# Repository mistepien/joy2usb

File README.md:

# joy2usb
Atari-like joystick adapter to USB.

<a href="https://github.com/mistepien/joy2usb/blob/main/joy2usb.pdf">Adapter</a> is actually a shield for 
<a href="https://learn.sparkfun.com/tutorials/pro-micro--fio-v3-hookup-guide/hardware-overview-pro-micro">Arduino Pro Micro based on ATmega 32U4</a>.

ATmega 32U4 has a hardware support for fullspeed USB, thus <a href="https://wiki.archlinux.org/title/mouse_polling_rate">polling rate 1000Hz</a> is not an issue for that chip.

You can use the <a href="https://github.com/mistepien/joy2usb/blob/main/production/joy2usb_6.2_2023-10-14_00-56-38/joy2usb_6.2.zip">gerber file<a> to order the PCB.

Attached   <a href="https://github.com/mistepien/joy2usb/blob/main/joy2usb.ino">code</a> uses port registers so that is quite efficient, debouncing is done without delay() function.

The adapter has a toggle C64/Amiga for choosing C64 or Amiga approach for FIRE2/FIRE3. According to <a href="http://wiki.icomp.de/wiki/DE-9_Joystick"> wiki.icomp.de website about DE-9 joystick</a>, FIRE2/FIRE3 are pulled to VCC in case of C64 and to GND in case of Amiga. That is not an issue for joy2usb due to XOR magic.

Two footprints are not trivial: DB9 male socket (<b>J1</b>) and SPDT switch (<b>SW2</b>).

Officialy the <b>J1</b> footprint (joy2usb has been designed in <a href="https://www.kicad.org/">KiCad</a>) is "DSUB-9_Male_Horizontal_P2.77x2.84mm_EdgePinOffset9.90mm_Housed_MountingHolesOffset11.32mm"
however it was chosen to fit <a href="https://www.tme.eu/pl/en/details/ld09p13a4gx00lf/d-sub-plugs-and-sockets/amphenol-communications-solutions/">   LD09P13A4GX00LF Amphenol</a>.

<b>SW2</b> supposed to be <a href="https://www.tme.eu/pl/en/details/mfp1220/slide-switches/knitter-switch/mfp-1220">Switch SPDT MFP 1220 KNITTER-SWITCH</a>, but it can be replaced with Pinheader 1x3/1x2 (pitch terminal 2.54mm) + jumper or any other SPDT switch with 3 pins and pitch terminal 2.54mm (e.g. <a href="https://www.tme.eu/pl/details/eg1218/przelaczniki-suwakowe/e-switch/">EG1218 E-SWITCH</a>).

<b>J2</b> is redundant -- you can use it to add some new features like autofire switch or sth. In attached firmware connecting PF4 to GND disables debouncing procedure. <b>If you connect PF5 to GND you can read FIRE1 CPS ("$cat /dev/ttyACM0" in Linux).</b>

Sometimes during uploading code to Arduino board you may face some issues -- then you will need to use RESET -- so <b>SW1</b> can be useful if you like to develope your own code.

BOM:
| Qty	| Reference(s) | Description |
|-----|--------------|-------------|
|3 | D1, D2, D3 | LEDs 3mm |  
|1 |	J1|	DB9 Male Connector <a href="https://www.tme.eu/pl/en/details/ld09p13a4gx00lf/d-sub-plugs-and-sockets/amphenol-communications-solutions/">   LD09P13A4GX00LF Amphenol</a> |
|1 |	J2|	2x4 Pinheader. pitch terminal: 2.54mm |
|3 | R1, R2, R3 | resistors for D1, D2 and D3 |
|2 | R4, R5	| resistors 10KΩ |
|1 | SW1 | Tact switch from Arduino breadboard projects |
|1 | SW2 | <a href="https://www.tme.eu/pl/en/details/mfp1220/slide-switches/knitter-switch/mfp-1220">Switch SPDT MFP 1220 KNITTER-SWITCH</a> |
|1 | U1 |	DIP20 socket (width 15.24mm) + <a href="https://learn.sparkfun.com/tutorials/pro-micro--fio-v3-hookup-guide/hardware-overview-pro-micro">Arduino Pro Micro</a> |

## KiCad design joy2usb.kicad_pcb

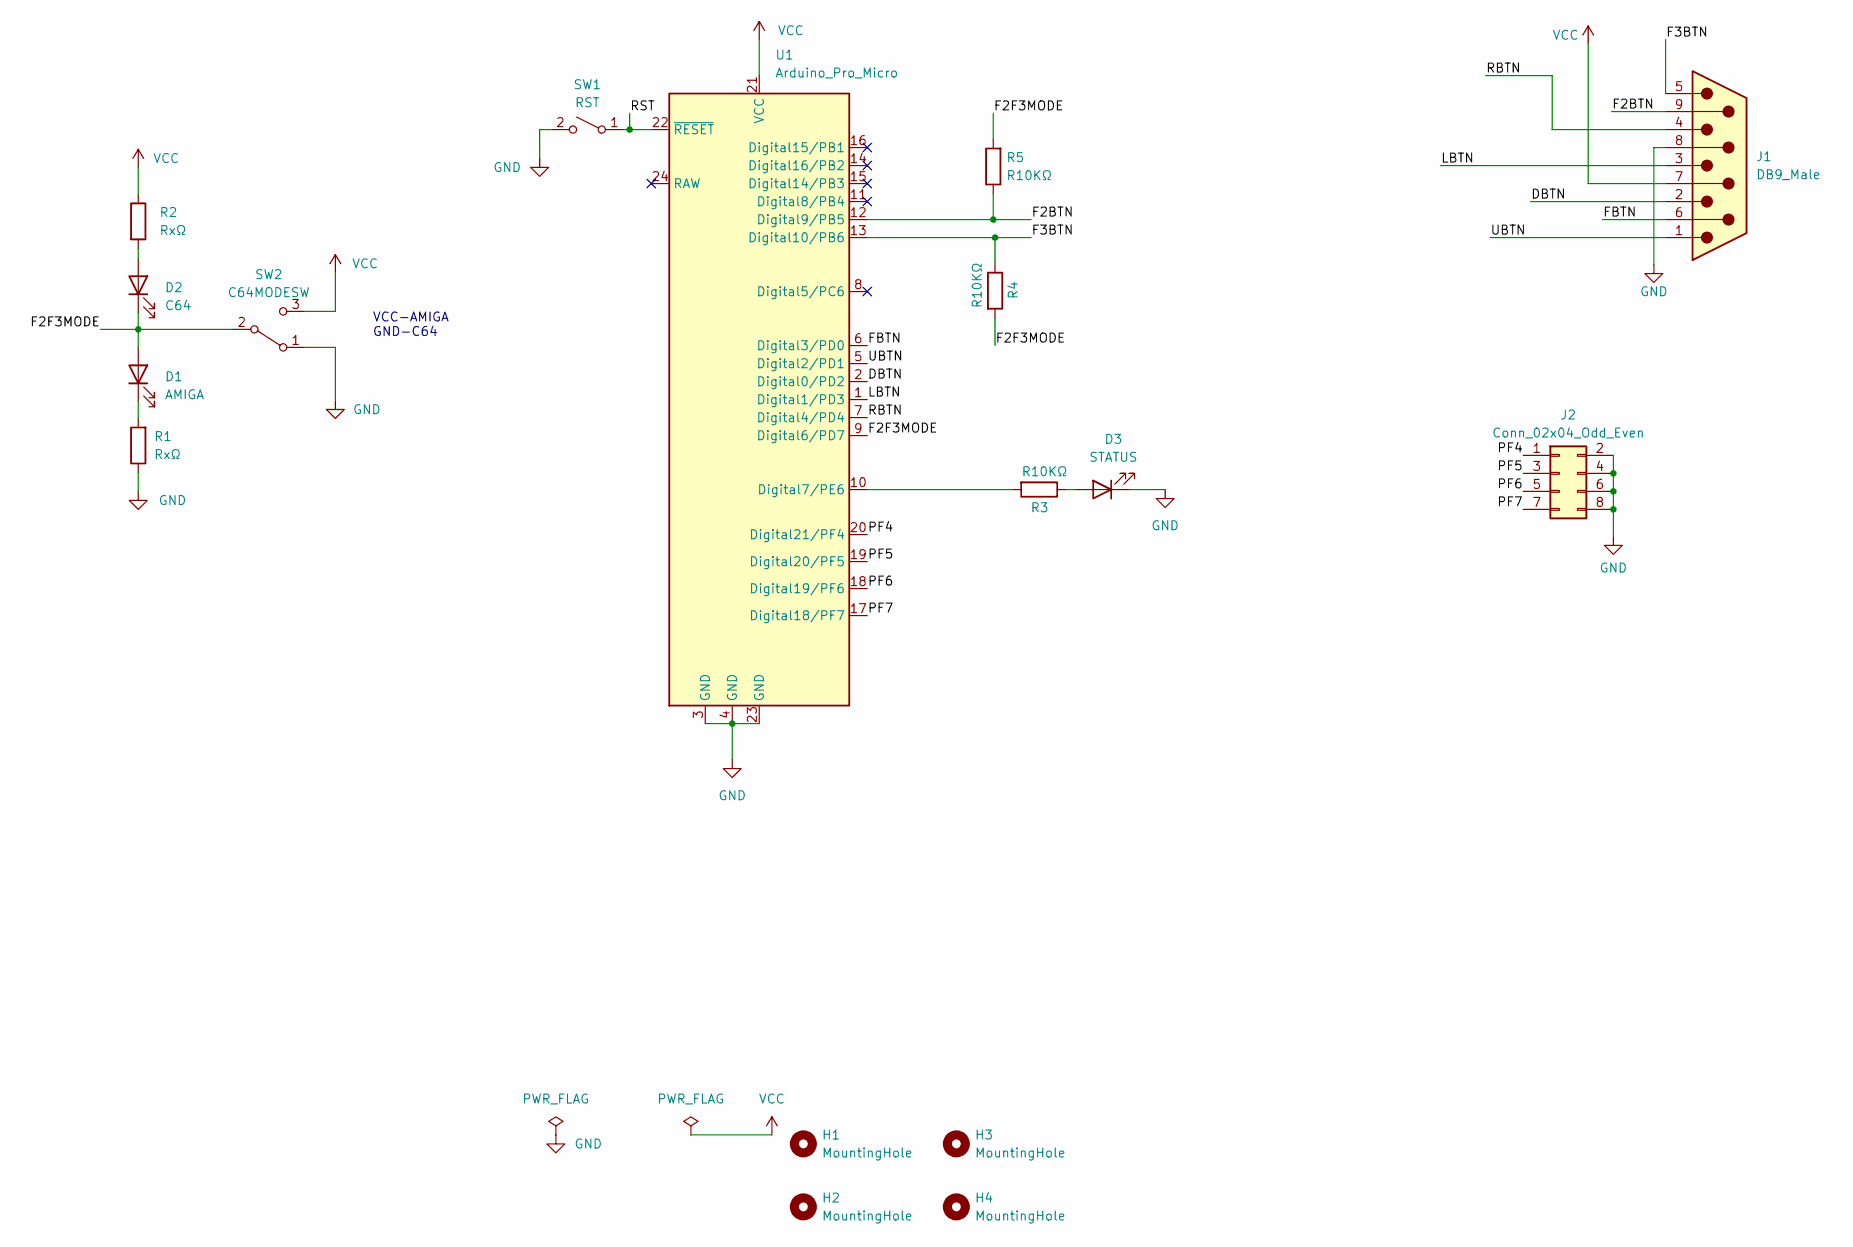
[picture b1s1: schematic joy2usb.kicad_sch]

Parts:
D1: AMIGA; LED_D3.0mm_Oval
D2: C64; LED_D3.0mm_Oval
D3: STATUS; LED_D3.0mm_Oval
H1, H2, H3, H4: MountingHole; MountingHole_3.5mm
J1: DB9_Male; DSUB-9_Male_Horizontal_P2.77x2.84mm_EdgePinOffset9.90mm_Hou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
J2: Conn_02x04_Odd_Even; PinHeader_2x04_P2.54mm_Vertical
R1, R2: RxΩ; R_Axial_DIN0207_L6.3mm_D2.5mm_P10.16mm_Horizontal_Oval
R3, R4, R5: R10KΩ; R_Axial_DIN0207_L6.3mm_D2.5mm_P10.16mm_Horizontal_Oval
SW1: RST; SW_PUSH_6mm_H4.3mm
SW2: C64MODESW; E-Switch-EG1218-Manufacturer_Recommended_Oval
U1: Arduino_Pro_Micro; DIP-24_W15.24mm_Socket_LongPads

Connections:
/DBTN: J1.2, U1.2 (Digital0/PD2)
/F2BTN: J1.9, R5.1, U1.12 (Digital9/PB5)
/F2F3MODE: D1.2 (A), D2.1 (K), R4.2, R5.2, SW2.2 (B), U1.9 (Digital6/PD7)
/F3BTN: J1.5, R4.1, U1.13 (Digital10/PB6)
/FBTN: J1.6, U1.6 (Digital3/PD0)
/LBTN: J1.3, U1.1 (Digital1/PD3)
/PF4: J2.1, U1.20 (Digital21/PF4)
/PF5: J2.3, U1.19 (Digital20/PF5)
/PF6: J2.5, U1.18 (Digital19/PF6)
/PF7: J2.7, U1.17 (Digital18/PF7)
/RBTN: J1.4, U1.7 (Digital4/PD4)
/RST: SW1.1 (A), U1.22 (~RESET)
/UBTN: J1.1, U1.5 (Digital2/PD1)
GND: D3.1 (K), J1.8, J2.2, J2.4, J2.6, J2.8, R1.1, SW1.2 (B), SW2.1 (A), U1.3 (GND), U1.4 (GND), U1.23 (GND)
unnamed: D1.1 (K), R1.2
unnamed: D2.2 (A), R2.2
unnamed: D3.2 (A), R3.1
unnamed: R3.2, U1.10 (Digital7/PE6)
VCC: J1.7, R2.1, SW2.3 (C), U1.21 (VCC)

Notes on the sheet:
VCC-AMIGA GND-C64

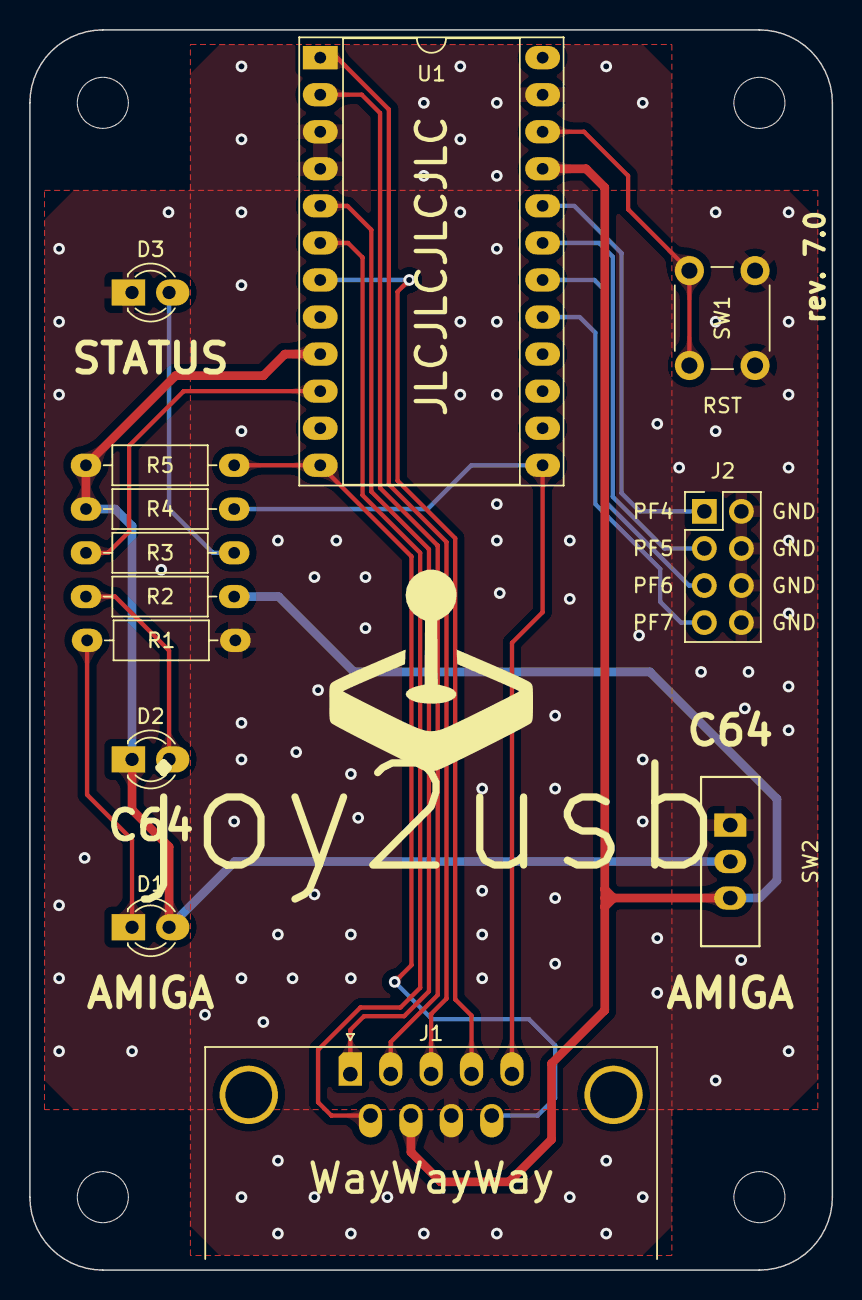
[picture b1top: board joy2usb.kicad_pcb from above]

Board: 2 copper layers, 55.0 x 85.0 mm, 17 parts (0 on the bottom side), 19 nets.

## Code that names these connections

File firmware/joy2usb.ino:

/*  joy2usb
 *  Author: mistepien@wp.pl
 *
 *  Copyright (c) 2022, 2023 Michał Stępień
 *
 *  GNU GENERAL PUBLIC LICENSE
 *  Version 3, 29 June 2007
 *
 *  This program is free software: you can redistribute it and/or modify
 *  it under the terms of the GNU General Public License as published by
 *  the Free Software Foundation, either version 3 of the License, or
 *  (at your option) any later version.
 *
 *  This program is distributed in the hope that it will be useful,
 *  but WITHOUT ANY WARRANTY; without even the implied warranty of
 *  MERCHANTABILITY or FITNESS FOR A PARTICULAR PURPOSE.  See the
 *  GNU General Public License for more details.
 *
 *  You should have received a copy of the GNU General Public License
 *  along with this program.  If not, see <https://www.gnu.org/licenses/>.
 *
 */



#include <Joystick.h>  //https://github.com/MHeironimus/ArduinoJoystickLibrary



//#define DEBUG

byte minimal_axis_time;
byte minimal_button_time;



#ifdef DEBUG
// for performance monitor
unsigned long timer = 0;
unsigned long loops = 0;
#define SEKUNDA 1000000
#endif



Joystick_ Joystick(JOYSTICK_DEFAULT_REPORT_ID, JOYSTICK_TYPE_JOYSTICK,
                   3, 0,            // Button Count, Hat Switch Count
                   true, true, false,     // X and Y, but no Z Axis
                   false, false, false,   // No Rx, Ry, or Rz
                   false, false,          // No rudder or throttle
                   false, false, false);  // No accelerator, brake, or steering


void debouncing(bool mode = 1) {
  if ( mode ) {
      minimal_axis_time = 8;
      minimal_button_time = 10;
  } else {
      minimal_axis_time = 0;
      minimal_button_time = 0;
  }
}

byte C64Mode = 0;

#define SAMPLES 10
void setup() {
DDRF &= ~bit(4); PORTF |= bit(4); //INPUT_PULLUP FOR DEBOUNCING SWITCH
  
DDRE &= ~bit(6); PORTE |= bit(6); //INPUT_PULLUP FOR C64/AMIGA MODE SWITCH
//READ C64/AMIGA MODE SWITCH STATE
  byte C64ModeTEMP = 0;  
  for (byte index = 0; index  < SAMPLES; index++) { 
  //READ C64/AMIGA SWITCH MODE
  delayMicroseconds(30);
  C64ModeTEMP = (1 ^ bitRead(PINE,6)) + C64ModeTEMP; 
  }
  if ( C64ModeTEMP / SAMPLES > 0.5 ) {
    C64Mode = 1;
  } else {
    C64Mode = 0;
  }

DDRC |= bit(6); //F2F3MODE as OUTPUT
PORTC &= ~bit(6); //F2F3MODE as LOW 

DDRD &= ~B00011111; PORTD |=  B00011111; //PD0-PD4 as INPUT_PULLUP


  Joystick.setXAxisRange(-1, 1);
  Joystick.setYAxisRange(-1, 1);
  Joystick.begin(false);
  Joystick.setXAxis(0);
  Joystick.setYAxis(0);
 
  delay(1500); /*very ugly and dirty hack
                without that delay() joystick will not
                be centered at the beginning (that is an
                issue with Joystick.sendState();
                */

DDRB &= ~B01100000; //INPUT for F2 and F3
if (C64Mode){ //FOR C64 -- INPUT + PULL_DOWN (via IC4066) -- INPUT IS SET ONE LINE ABOVE
  PORTC |= bit(6); //F2F3MODE as HIGH
} else {      //FOR AMIGA -- INPUT_PULLUP + NO PULL_DOWN (switches in IC4066 are off)
  PORTB |= B01100000; //INPUT_PULLUP for F2 and F3
  PORTC &= ~bit(6); //F2F3MODE as LOW 
}

debouncing(bitRead(PINF,4));

Joystick.sendState();

/*turn off RX and TX LEDS
 * on permanent basis
 * 
 * turning off these LEDS here at the end of setup()
 * is an indicator that joy2usb is ready
 */
bitClear(DDRD,5);
bitClear(DDRB,0);
}


unsigned long prev_button_time[3] = { 0, 0, 0 };
unsigned long prev_axis_time[4] = { 0, 0, 0, 0 };
byte JOY_D = 0;
byte JOY_U = 0;
byte JOY_R = 0;
byte JOY_L = 0;
byte prev_axises;
byte prev_buttons;

void loop() {
byte pinb;
byte pind;
byte current_state;


pind = ~PIND & B00011111; //clear PD5,PD6 and PD7
if (C64Mode){
pinb =  PINB & B01100000; //INPUT LOGIC + clear all except PB5 and PB6
} else {
pinb = ~PINB & B01100000; //INPUT_PULLUP LOGIC -- inverted + clear all except PB5 and PB6
}
byte current_axises = pind >> 1; //0,1 -- Y axis, 2,3 -X axis
byte current_buttons = (pind & B00000001) | (pinb >> 4); /* eg. B00000111 (when F1, F2 and F3
                                                          are pressed the same time)
                                                          -- bit number is number of button */
//Serial.println(current_axises, BIN);

byte changedAxises = current_axises ^ prev_axises;
byte changedButtons = current_buttons ^ prev_buttons;

if ( changedAxises || changedButtons ) {
unsigned long current_time = millis(); //ONE common millis() for AXISES AND BUTTONS SECTIONS

if ( changedAxises ) { //AXISES SECTION


byte axisXchanged = 0;
byte axisYchanged = 0;
    for (byte index = 0; index < 4; index++) {
      if (bitRead(changedAxises,index)) {
        if (current_time - prev_axis_time[index] > minimal_axis_time) {
          prev_axis_time[index] = current_time;
          prev_axises = current_axises;

          current_state = bitRead(current_axises,index);
          switch (index) {
            case 0: //UP
              JOY_U = current_state; axisYchanged = 1;
              break;
            case 1: //DOWN
              JOY_D = current_state; axisYchanged = 1;
              break;
            case 2: //LEFT
              JOY_L = current_state; axisXchanged = 1;
              break;
            case 3: //RIGHT
              JOY_R = current_state; axisXchanged = 1;
              break;
          }
        }
      }
    }
    if ( axisYchanged ) {
      if ( ( JOY_U ) && ( JOY_D ) ) {
            JOY_D = 1 ^ JOY_D;
          }
      Joystick.setYAxis(JOY_D - JOY_U);
      }
    if ( axisXchanged ) {
      if ( ( JOY_L ) && ( JOY_R ) ) {
            JOY_R = 1 ^ JOY_R;
            JOY_L = 1 ^ JOY_L;
          }
      Joystick.setXAxis(JOY_R - JOY_L);
    }
}

  if ( changedButtons ) { //BUTTONS SECTION
    for (byte index = 0; index < 3; index++) {
       if (bitRead(changedButtons,index)) {
        if (current_time - prev_button_time[index] > minimal_button_time) {
          prev_button_time[index] = current_time;
          prev_buttons = current_buttons;

          current_state = bitRead(current_buttons,index);
          Joystick.setButton(index, current_state);
        }
       }
    }
  }
   Joystick.sendState(); //ONE common send.State for AXISES AND BUTTONS SECTIONS
}

#ifdef DEBUG
    // PERFORMANCE MONITOR
    // it shows how many loops are executed in 1s
    if (micros() - timer >= SEKUNDA) {
      Serial.print("loop() cycles in last second: ");
      Serial.println(loops);
      loops = 0;
      timer = micros();
    }
    loops++;  //increassing a counter
#endif
}

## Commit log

2022-11-04 Initial commit rev. 1.0
2022-11-05 Fixing of annoying bug
2022-11-06 Use port registers even more
2022-11-07 PCB Rev. 2.0
    Diode D1 is turned on in the same way as PULL-DOWN for the C64 Mode. Thus when D1 is on it means that PULL-DOWN for the C64 Mode is on, too.
2022-11-07 PCB Rev. 2.0
2022-11-11 PCB Rev. 2.1
    Slightly wider signal tracks and better symmetry.
2022-11-19 PCB Rev. 2.2
    Bigger mass field
2022-11-20 PCB Rev. 2.3
    Update of footprints -- oval pads
2022-11-20 Upload svg files
2022-11-20 PCB Rev. 2.3
2022-11-20 PCB Rev. 2.3
    Updated pads
2022-11-28 Schematic Rev. 2.1
    few cosmetic updates
2022-11-29 PCB Rev. 2.4
    update: rounded corners
2022-11-29 PCB Rev. 2.41
    fix: update of nets
2022-12-07 fixing problem with C64 mode startup
    Arduino micro clone has some issues with reading pins in setup().
2022-12-11 PCB Rev. 2.5
2022-12-11 PCB Rev. 2.5
    Update of LED footprint
2022-12-18 PCB Rev. 3.0
    Replace GND1 and GND2 with GND.
2022-12-18 PCB Rev. 3.1
    Several cosmetic PCB updates
2023-01-10 Shorter delay time in setup()
2023-01-10 Shorter delay time in setup() +
    + fixing problem with C64 mode startup
2023-01-21 PCB Rev. 4.0
    update C64/Amiga switch
2023-05-19 PCB Rev. 4.1
    SW2 minor amendment
2023-05-19 Update README.md
    adding information about EG1218 E-SWITCH
2023-06-07 PCB Rev. 5.0
    Minor update of DB9 socket footprint.
2023-06-25 New feature: option to disable debouncing
    New feature: option to disable debouncing
    To disable debouncing short PF4 and GND (eg. with jumper). Useful for "gamepad to db9" joystick adapters.
2023-07-04 Reliable checking of C64 MODE switch in setu()
2023-10-13 PCB Rev. 6.2
    removal of ic 4066
2023-10-13 PCB Rev. 6.2
    removal of ic 4066
2023-10-28 PCB Rev. 6.3
    WayWayWay text on silkscreen for PCBWay is added
2024-01-31 rev. 6.3
    update of description of one resistor
2024-02-03 joy2usb can be used to measure fire1 CPS
    Quite useful for finding autofire CPS of legacy joysticks.
2024-02-03 joy2usb can be used to measure fire1 CPS
2024-02-29 added teardrops
